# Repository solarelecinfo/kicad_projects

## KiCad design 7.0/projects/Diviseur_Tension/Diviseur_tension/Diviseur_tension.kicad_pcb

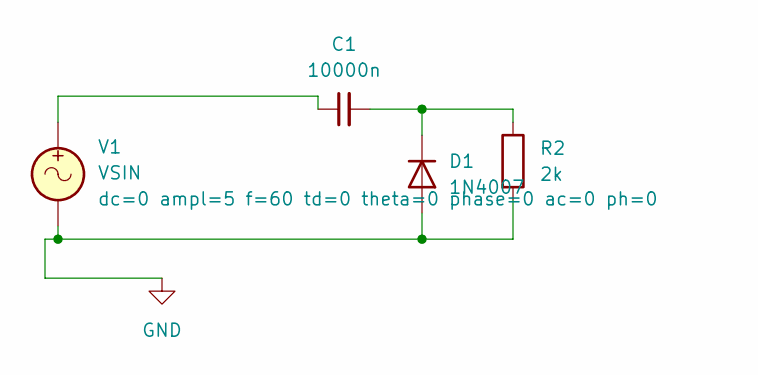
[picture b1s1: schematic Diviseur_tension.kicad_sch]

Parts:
C1: 10000n; PinHeader_1x02_P2.54mm_Vertical
D1: 1N4007; D_DO-41_SOD81_P10.16mm_Horizontal
R2: 2k; R_Axial_DIN0516_L15.5mm_D5.0mm_P7.62mm_Vertical
V1: VSIN; PinHeader_1x02_P2.54mm_Vertical

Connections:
GND: D1.2 (A), R2.2, V1.2
unnamed: C1.1, V1.1
unnamed: C1.2, D1.1 (K), R2.1

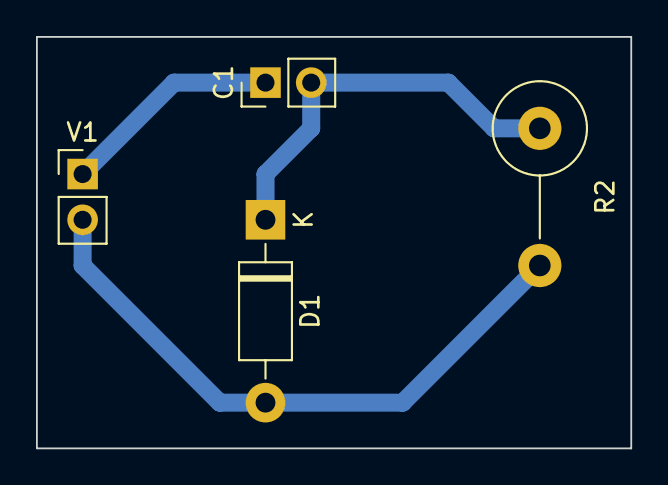
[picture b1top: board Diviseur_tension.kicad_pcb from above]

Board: 2 copper layers, 33.0 x 22.9 mm, 4 parts (0 on the bottom side), 3 nets.

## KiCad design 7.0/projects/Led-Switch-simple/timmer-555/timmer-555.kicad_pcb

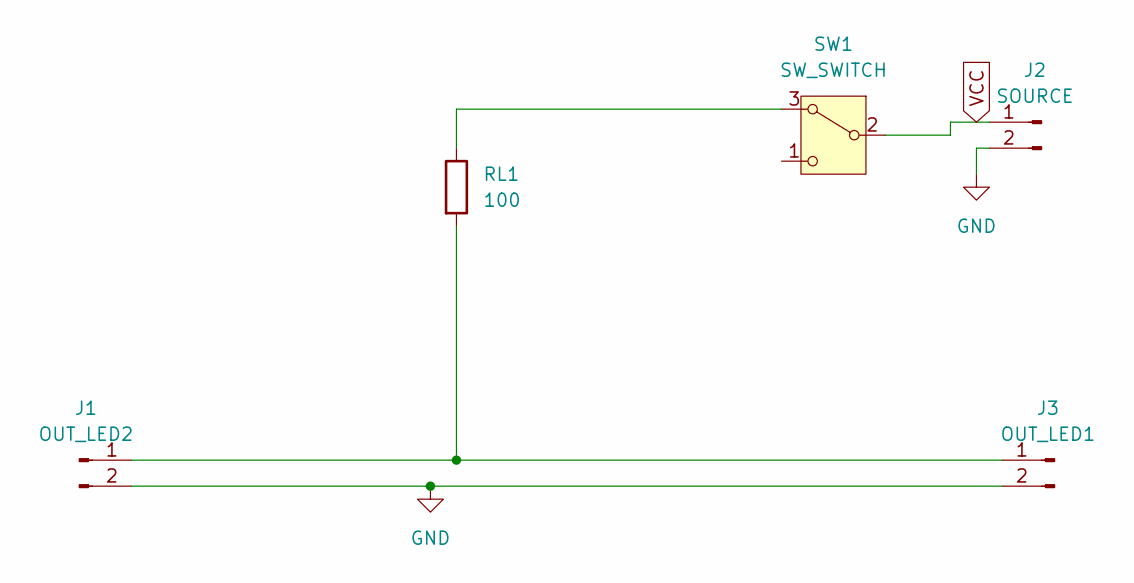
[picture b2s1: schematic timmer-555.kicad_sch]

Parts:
J1: OUT_LED2; TerminalBlock_MetzConnect_Type094_RT03502HBLU_1x02_P5.00mm_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
J2: SOURCE; TerminalBlock_MetzConnect_Type094_RT03502HBLU_1x02_P5.00mm_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
J3: OUT_LED1; TerminalBlock_MetzConnect_Type094_RT03502HBLU_1x02_P5.00mm_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
RL1: 100; R_Axial_DIN0207_L6.3mm_D2.5mm_P7.62mm_Horizontal
SW1: SW_SWITCH; TerminalBlock_bornier-3_P5.08mm

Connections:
GND: J1.2, J2.2, J3.2
unnamed: J1.1, J3.1, RL1.2
unnamed: RL1.1, SW1.3 (A)
VCC: J2.1, SW1.2 (B)

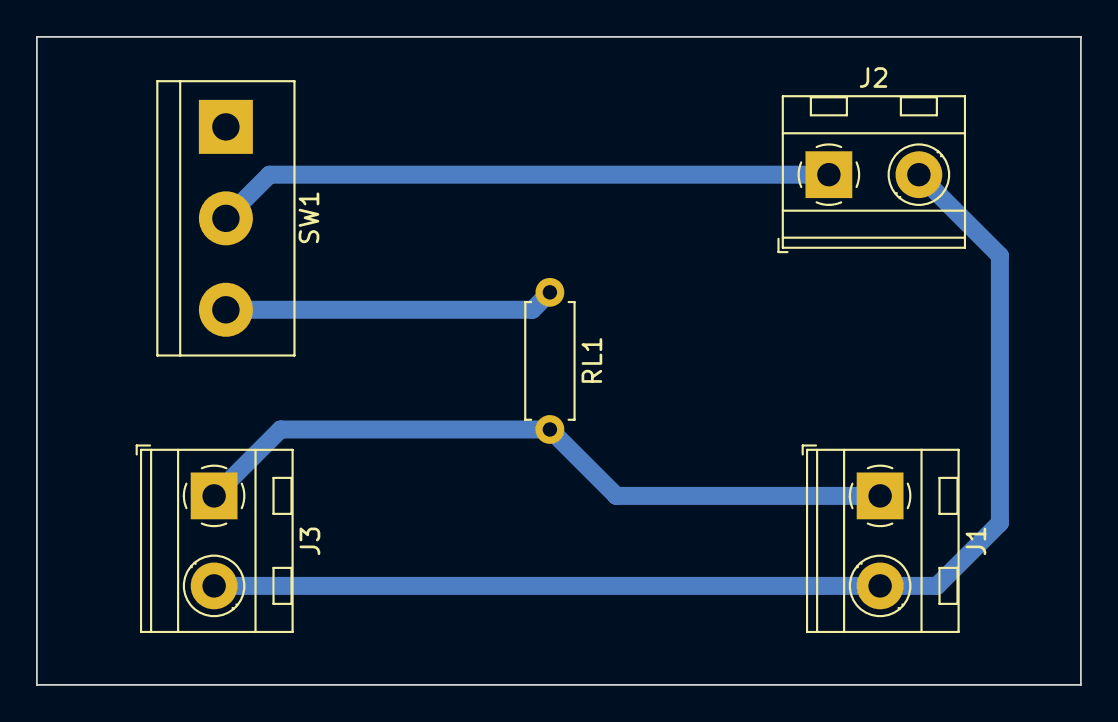
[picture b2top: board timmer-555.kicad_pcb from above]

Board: 2 copper layers, 58.0 x 36.0 mm, 5 parts (0 on the bottom side), 4 nets.

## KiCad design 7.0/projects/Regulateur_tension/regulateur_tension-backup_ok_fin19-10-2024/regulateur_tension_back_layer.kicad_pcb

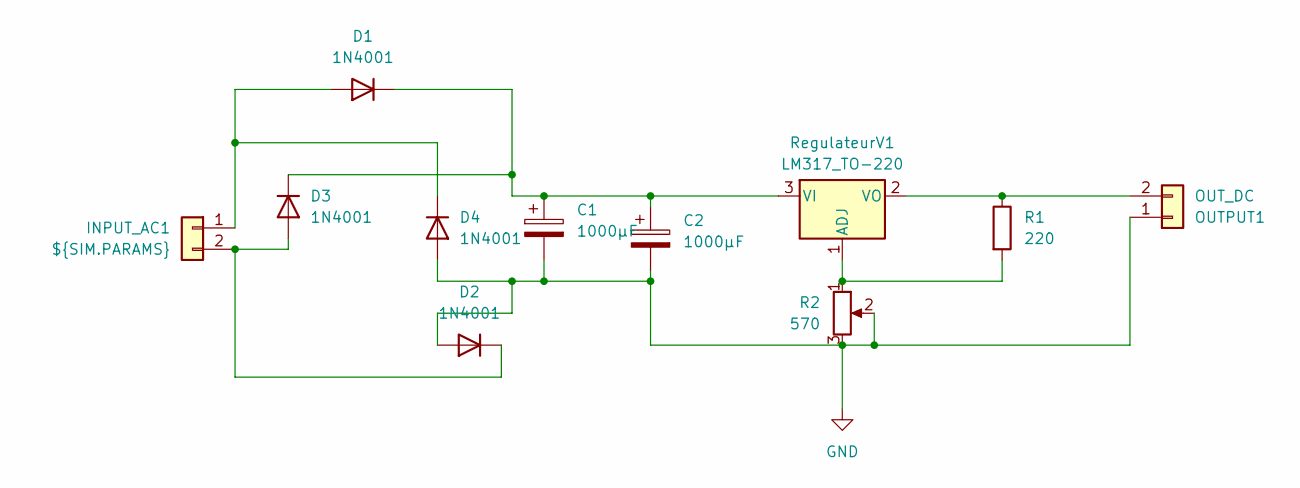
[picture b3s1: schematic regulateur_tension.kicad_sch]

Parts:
C1, C2: 1000μF; CP_Radial_D13.0mm_P7.50mm
D1, D2, D3, D4: 1N4001; D_DO-41_SOD81_P10.16mm_Horizontal
INPUT_AC1: ${SIM.PARAMS}; TerminalBlock_MetzConnect_Type094_RT03502HBLU_1x02_P5.00mm_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
OUTPUT1: OUT_DC; TerminalBlock_MetzConnect_Type094_RT03502HBLU_1x02_P5.00mm_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
R1: 220; R_Axial_DIN0207_L6.3mm_D2.5mm_P5.08mm_Vertical
R2: 570; Potentiometer_Piher_PC-16_Single_Vertical
RegulateurV1: LM317_TO-220; TO-220-3_Vertical

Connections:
GND: C1.2, C2.2, D2.2 (A), D4.2 (A), OUTPUT1.1, R2.2, R2.3
unnamed: D1.2 (A), D4.1 (K), INPUT_AC1.1
unnamed: C1.1, C2.1, D1.1 (K), D3.1 (K), RegulateurV1.3 (VI)
unnamed: D2.1 (K), D3.2 (A), INPUT_AC1.2
unnamed: OUTPUT1.2, R1.1, RegulateurV1.2 (VO)
unnamed: R1.2, R2.1, RegulateurV1.1 (ADJ)

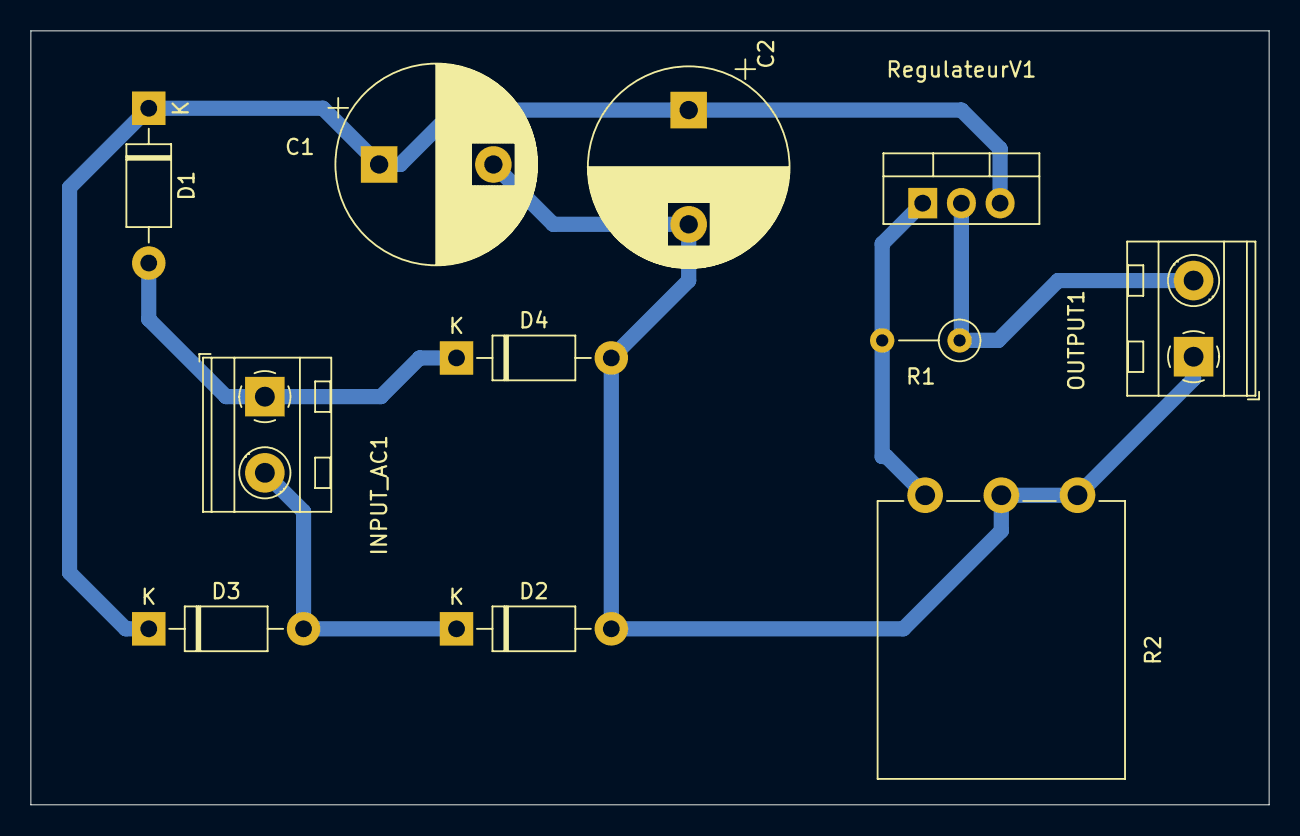
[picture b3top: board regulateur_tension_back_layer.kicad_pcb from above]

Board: 2 copper layers, 81.3 x 50.8 mm, 11 parts (0 on the bottom side), 6 nets.
